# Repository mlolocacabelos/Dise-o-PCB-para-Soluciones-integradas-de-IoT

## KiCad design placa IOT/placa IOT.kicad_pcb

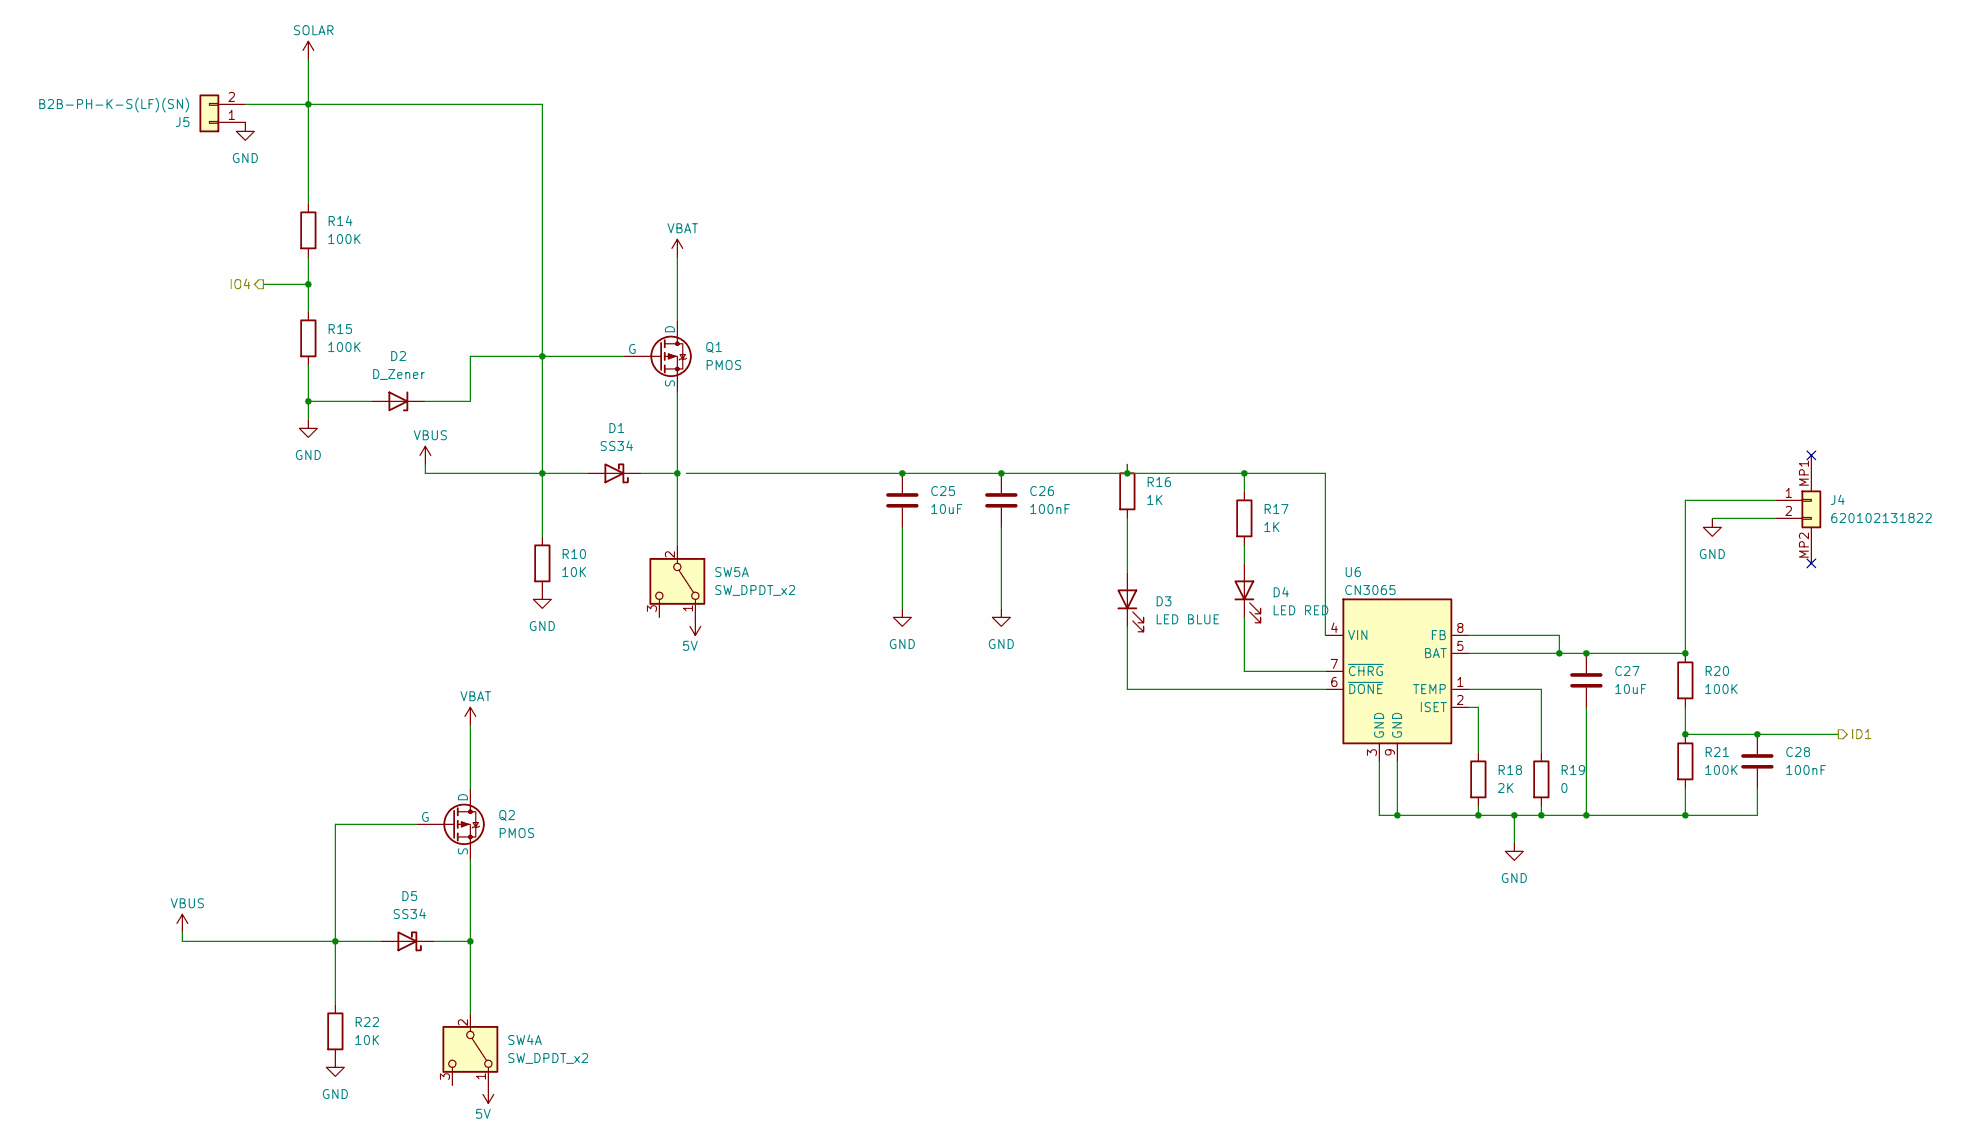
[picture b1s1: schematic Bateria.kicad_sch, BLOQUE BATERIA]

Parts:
C25, C27: 10uF; C_0402_1005Metric
C26, C28: 100nF; C_0402_1005Metric
D1, D5: SS34; D_SMA
D2: D_Zener; D_SOD-123
D3: LED BLUE; LED_0402_1005Metric
D4: LED RED; LED_0402_1005Metric
J4: 620102131822; CONN_SMT_MH_SH_P2.00MM_P2
J5: B2B-PH-K-S(LF)(SN); CONN_THT_MV_JST_P2.00MM_P2
Q1, Q2: PMOS; SOT-23-3
R10, R22: 10K; R_0402_1005Metric
R14, R15, R20, R21: 100K; R_0402_1005Metric
R16, R17: 1K; R_0402_1005Metric
R18: 2K; R_0402_1005Metric
R19: 0; R_0402_1005Metric
SW4, SW5: SW_DPDT_x2; SW_Slide_SPDT_Angled_CK_OS102011MA1Q
U6: CN3065; DFN-8-1EP_3x3mm_P0.5mm_EP1.66x2.38mm

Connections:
5V: SW4.1 (A), SW5.1 (A)
/MCU_WIFIBLU/IO1: C28.1, R20.2, R21.1; also elsewhere on the board
/MCU_WIFIBLU/IO4: R14.2, R15.1; also elsewhere on the board
GND: C25.2, C26.2, C27.2, C28.2, D2.2 (A), J4.2, J5.1, R10.2, R15.2, R18.2, R19.2, R21.2, R22.2, U6.3 (GND), U6.9 (GND); also elsewhere on the board
unnamed: D1.1 (K), Q1.3 (S), SW5.2 (B)
unnamed: D3.2 (A), R16.2
unnamed: D3.1 (K), U6.6 (~DONE)
unnamed: D4.2 (A), R17.2
unnamed: D4.1 (K), U6.7 (~CHRG)
unnamed: D5.1 (K), Q2.3 (S), SW4.2 (B)
unnamed: C27.1, J4.1, R20.1, U6.5 (BAT), U6.8 (FB)
unnamed: R18.1, U6.2 (ISET)
unnamed: R19.1, U6.1 (TEMP)
unnamed: C25.1, C26.1, R16.1, R17.1, U6.4 (VIN)
SOLAR: D1.2 (A), D2.1 (K), D5.2 (A), J5.2, Q1.2 (G), Q2.2 (G), R10.1, R14.1, R22.1; also elsewhere on the board
VBAT: Q1.1 (D), Q2.1 (D); also elsewhere on the board

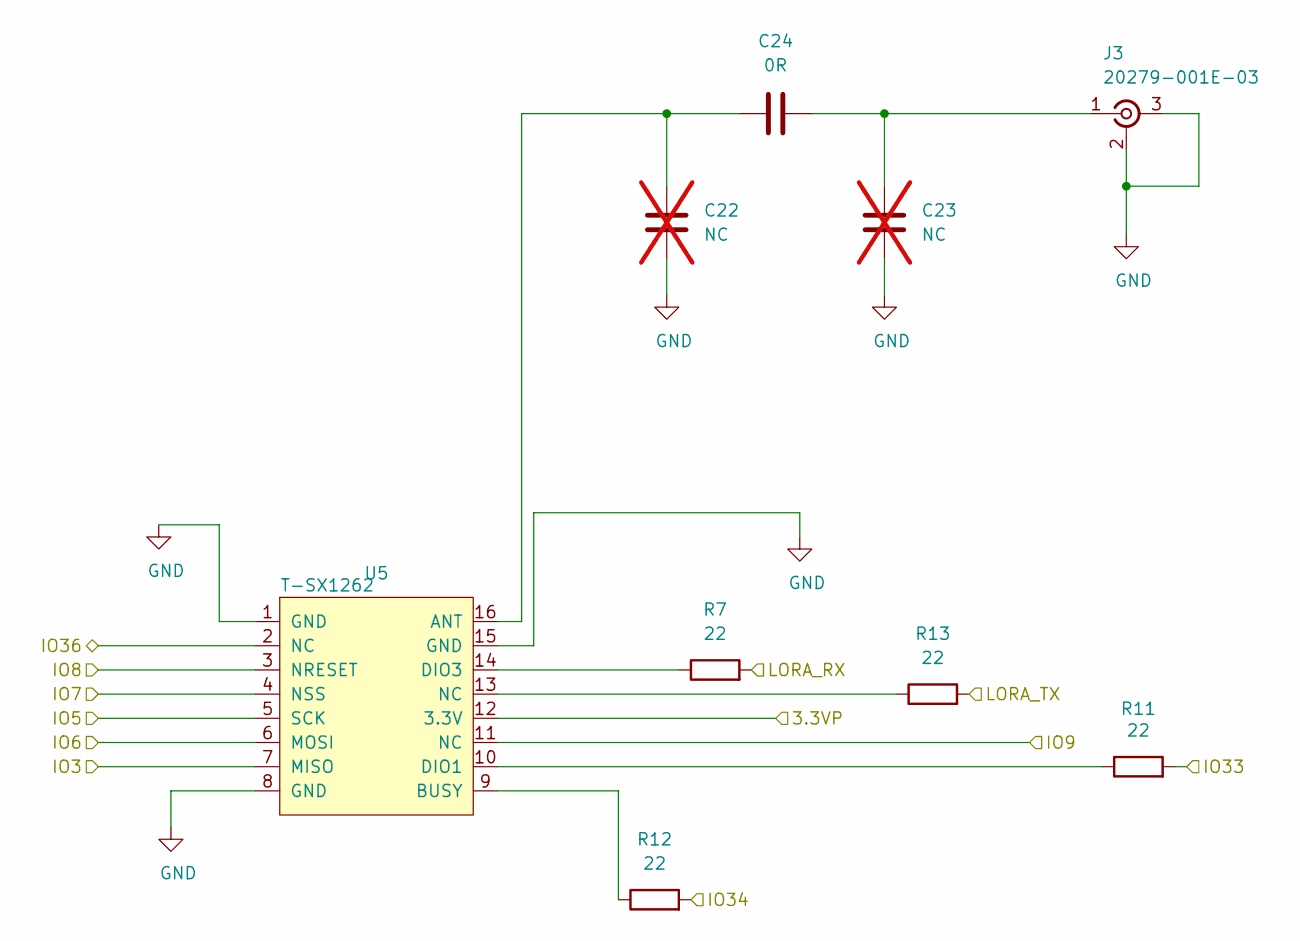
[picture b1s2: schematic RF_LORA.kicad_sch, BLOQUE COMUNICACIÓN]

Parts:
C22, C23: NC; C_0402_1005Metric; not fitted
C24: 0R; C_0402_1005Metric
J3: 20279-001E-03; IPEX_MHF_I
R7, R11, R12, R13: 22; R_0402_1005Metric
U5: T-SX1262; MODULE_T_SX1262

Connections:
/MCU_WIFIBLU/IO3: U5.7 (MISO); also elsewhere on the board
/MCU_WIFIBLU/IO5: U5.5 (SCK); also elsewhere on the board
/MCU_WIFIBLU/IO6: U5.6 (MOSI); also elsewhere on the board
/MCU_WIFIBLU/IO7: U5.4 (NSS); also elsewhere on the board
/MCU_WIFIBLU/IO8: U5.3 (NRESET); also elsewhere on the board
/MCU_WIFIBLU/IO9: U5.11 (NC); also elsewhere on the board
/MCU_WIFIBLU/IO33: R11.2; also elsewhere on the board
/MCU_WIFIBLU/IO34: R12.2; also elsewhere on the board
/MCU_WIFIBLU/IO36: U5.2 (NC); also elsewhere on the board
/MCU_WIFIBLU/LORA_RX: R7.2; also elsewhere on the board
/MCU_WIFIBLU/LORA_TX: R13.2; also elsewhere on the board
/RF_LORA/3.3VP: U5.12 (3.3V)
GND: C22.2, C23.2, J3.2 (Ext), J3.3 (Ext), U5.1 (GND), U5.8 (GND), U5.15 (GND); also elsewhere on the board
unnamed: C23.1, C24.2, J3.1 (In)
unnamed: R13.1, U5.13 (NC)
unnamed: C22.1, C24.1, U5.16 (ANT)
unnamed: R12.1, U5.9 (BUSY)
unnamed: R11.1, U5.10 (DIO1)
unnamed: R7.1, U5.14 (DIO3)

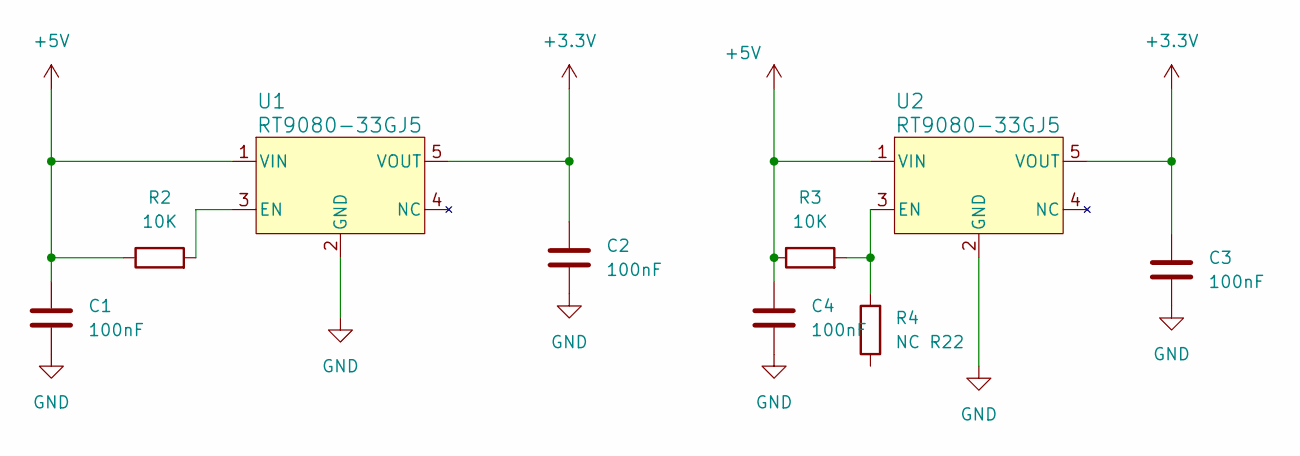
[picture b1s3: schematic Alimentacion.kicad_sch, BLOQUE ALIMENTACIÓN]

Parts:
C1, C2, C3, C4: 100nF; C_0402_1005Metric
R2, R3: 10K; R_0402_1005Metric
R4: NC R22; R_0402_1005Metric
U1, U2: RT9080-33GJ5; TSOT-23-5_RIT

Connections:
+3.3V: C2.1, C3.1, U1.5 (VOUT), U2.5 (VOUT); also elsewhere on the board
+5V: C1.1, C4.1, R2.1, R3.1, U1.1 (VIN), U2.1 (VIN)
GND: C1.2, C2.2, C3.2, C4.2, U1.2 (GND), U2.2 (GND); also elsewhere on the board
unnamed: R2.2, U1.3 (EN)
unnamed: R3.2, R4.2, U2.3 (EN)

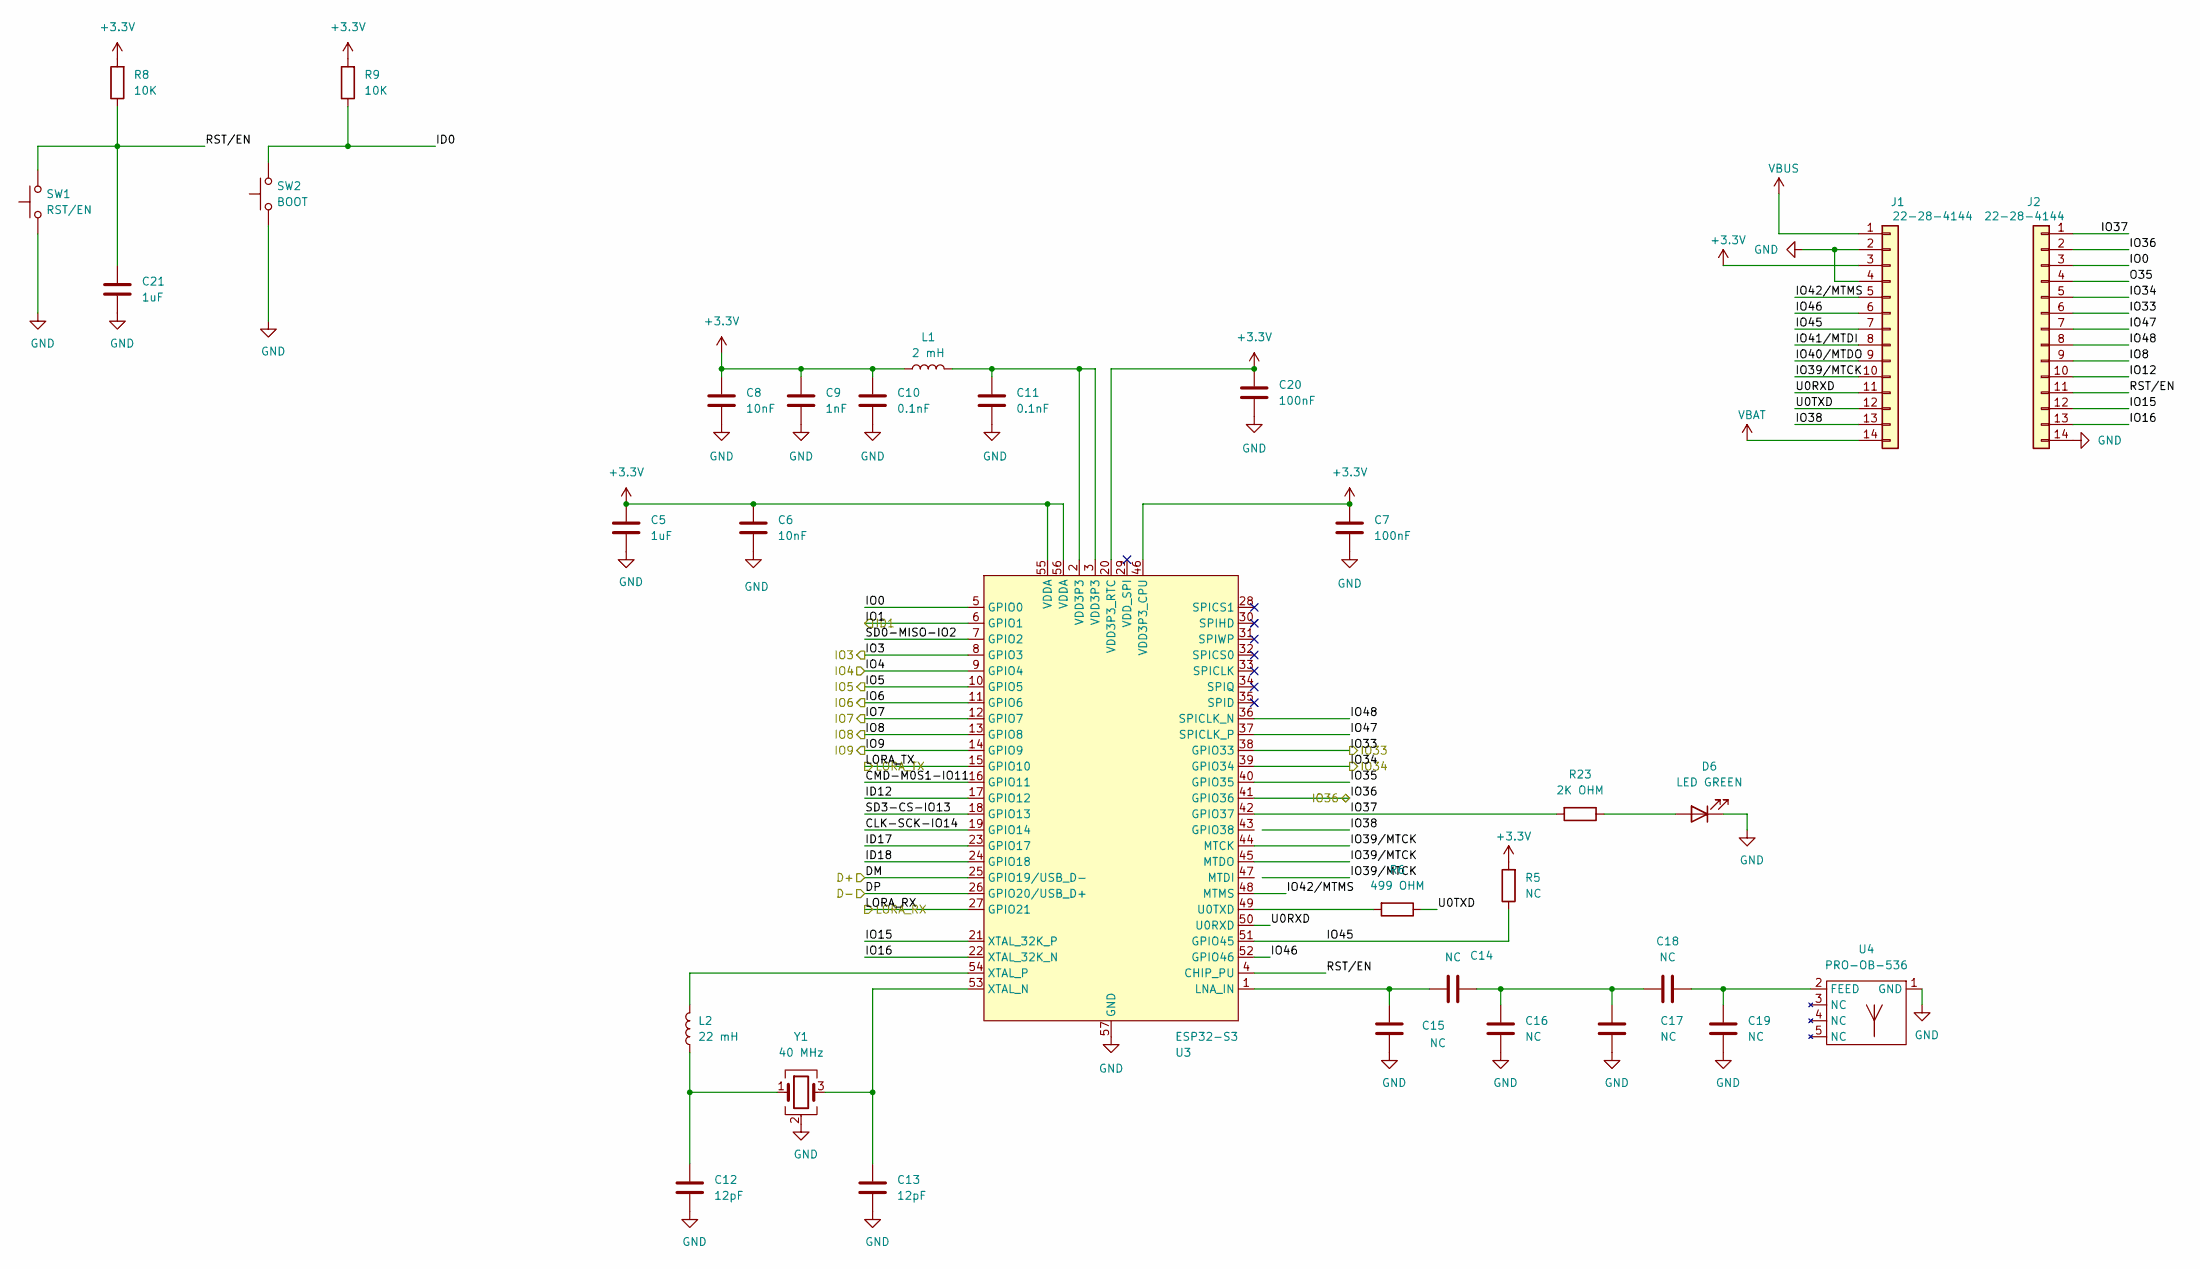
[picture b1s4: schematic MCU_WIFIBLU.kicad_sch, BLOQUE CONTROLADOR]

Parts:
C5, C21: 1uF; C_0402_1005Metric
C6, C8: 10nF; C_0402_1005Metric
C7, C20: 100nF; C_0402_1005Metric
C9: 1nF; C_0402_1005Metric
C10, C11: 0.1nF; C_0402_1005Metric
C12, C13: 12pF; C_0402_1005Metric
C14, C15, C16, C17, C18, C19: NC; C_0402_1005Metric
D6: LED GREEN; LED_0402_1005Metric
J1, J2: 22-28-4144; CONN_THT_MV_PH_P2.54MM_P14
L1: 2 mH; L_0402_1005Metric
L2: 22 mH; L_0402_1005Metric
R5: NC; R_0402_1005Metric
R6: 499 OHM; R_0402_1005Metric
R8, R9: 10K; R_0402_1005Metric
R23: 2K OHM; R_0402_1005Metric
SW1: RST/EN; SW_Push_SPST_NO_Alps_SKRK
SW2: BOOT; SW_Push_SPST_NO_Alps_SKRK
U3: ESP32-S3; QFN-56-1EP_7x7mm_P0.4mm_EP4x4mm
U4: PRO-OB-536; ANTENNA_PIFA_3D_2.4GHZ
Y1: 40 MHz; Crystal_SMD_3225-4Pin_3.2x2.5mm

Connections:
+3.3V: C5.1, C6.1, C7.1, C8.1, C9.1, C10.1, C20.1, J1.3, L1.1, R5.2, R8.2, R9.2, U3.20 (VDD3P3_RTC), U3.46 (VDD3P3_CPU), U3.55 (VDDA), U3.56 (VDDA); also elsewhere on the board
/MCU_WIFIBLU/CLK-SCK-IO14: U3.19 (GPIO14)
/MCU_WIFIBLU/CMD-M0S1-IO11: U3.16 (GPIO11)
/MCU_WIFIBLU/DM: U3.25 (GPIO19/USB_D-); also elsewhere on the board
/MCU_WIFIBLU/DP: U3.26 (GPIO20/USB_D+); also elsewhere on the board
/MCU_WIFIBLU/ID0: R9.1, SW2.2
/MCU_WIFIBLU/ID12: U3.17 (GPIO12)
/MCU_WIFIBLU/ID17: U3.23 (GPIO17)
/MCU_WIFIBLU/ID18: U3.24 (GPIO18)
/MCU_WIFIBLU/IO0: J2.3, U3.5 (GPIO0)
/MCU_WIFIBLU/IO1: U3.6 (GPIO1); also elsewhere on the board
/MCU_WIFIBLU/IO3: U3.8 (GPIO3); also elsewhere on the board
/MCU_WIFIBLU/IO4: U3.9 (GPIO4); also elsewhere on the board
/MCU_WIFIBLU/IO5: U3.10 (GPIO5); also elsewhere on the board
/MCU_WIFIBLU/IO6: U3.11 (GPIO6); also elsewhere on the board
/MCU_WIFIBLU/IO7: U3.12 (GPIO7); also elsewhere on the board
/MCU_WIFIBLU/IO8: J2.9, U3.13 (GPIO8); also elsewhere on the board
/MCU_WIFIBLU/IO9: U3.14 (GPIO9); also elsewhere on the board
/MCU_WIFIBLU/IO12: J2.10
/MCU_WIFIBLU/IO15: J2.12, U3.21 (XTAL_32K_P)
/MCU_WIFIBLU/IO16: J2.13, U3.22 (XTAL_32K_N)
/MCU_WIFIBLU/IO33: J2.6, U3.38 (GPIO33); also elsewhere on the board
/MCU_WIFIBLU/IO34: J2.5, U3.39 (GPIO34); also elsewhere on the board
/MCU_WIFIBLU/IO35: U3.40 (GPIO35)
/MCU_WIFIBLU/IO36: J2.2, U3.41 (GPIO36); also elsewhere on the board
/MCU_WIFIBLU/IO37: J2.1, R23.2, U3.42 (GPIO37)
/MCU_WIFIBLU/IO38: J1.13
/MCU_WIFIBLU/IO39/MTCK: J1.10, U3.44 (MTCK), U3.45 (MTDO)
/MCU_WIFIBLU/IO40/MTDO: J1.9
/MCU_WIFIBLU/IO41/MTDI: J1.8
/MCU_WIFIBLU/IO42/MTMS: J1.5, U3.48 (MTMS)
/MCU_WIFIBLU/IO45: J1.7, R5.1, U3.51 (GPIO45)
/MCU_WIFIBLU/IO46: J1.6, U3.52 (GPIO46)
/MCU_WIFIBLU/IO47: J2.7, U3.37 (SPICLK_P)
/MCU_WIFIBLU/IO48: J2.8, U3.36 (SPICLK_N)
/MCU_WIFIBLU/LORA_RX: U3.27 (GPIO21); also elsewhere on the board
/MCU_WIFIBLU/LORA_TX: U3.15 (GPIO10); also elsewhere on the board
/MCU_WIFIBLU/O35: J2.4
/MCU_WIFIBLU/RST/EN: C21.1, J2.11, R8.1, SW1.2, U3.4 (CHIP_PU)
/MCU_WIFIBLU/SD0-MISO-IO2: U3.7 (GPIO2)
/MCU_WIFIBLU/SD3-CS-IO13: U3.18 (GPIO13)
/MCU_WIFIBLU/U0RXD: J1.11, U3.50 (U0RXD)
/MCU_WIFIBLU/U0TXD: J1.12, R6.1
GND: C5.2, C6.2, C7.2, C8.2, C9.2, C10.2, C11.2, C12.2, C13.2, C15.2, C16.2, C17.2, C19.2, C20.2, C21.2, D6.1 (K), J1.2, J1.4, J2.14, SW1.1, SW2.1, U3.57 (GND), U4.1 (GND), Y1.2 (G), Y1.4 (G); also elsewhere on the board
unnamed: C11.1, L1.2, U3.2 (VDD3P3), U3.3 (VDD3P3)
unnamed: C12.1, L2.1, Y1.1
unnamed: C14.2, C16.1, C17.1, C18.1
unnamed: D6.2 (A), R23.1
unnamed: C14.1, C15.1, U3.1 (LNA_IN)
unnamed: R6.2, U3.49 (U0TXD)
unnamed: C13.1, U3.53 (XTAL_N), Y1.3
unnamed: L2.2, U3.54 (XTAL_P)
unnamed: C18.2, C19.1, U4.2 (FEED)
SOLAR: J1.1; also elsewhere on the board
VBAT: J1.14; also elsewhere on the board

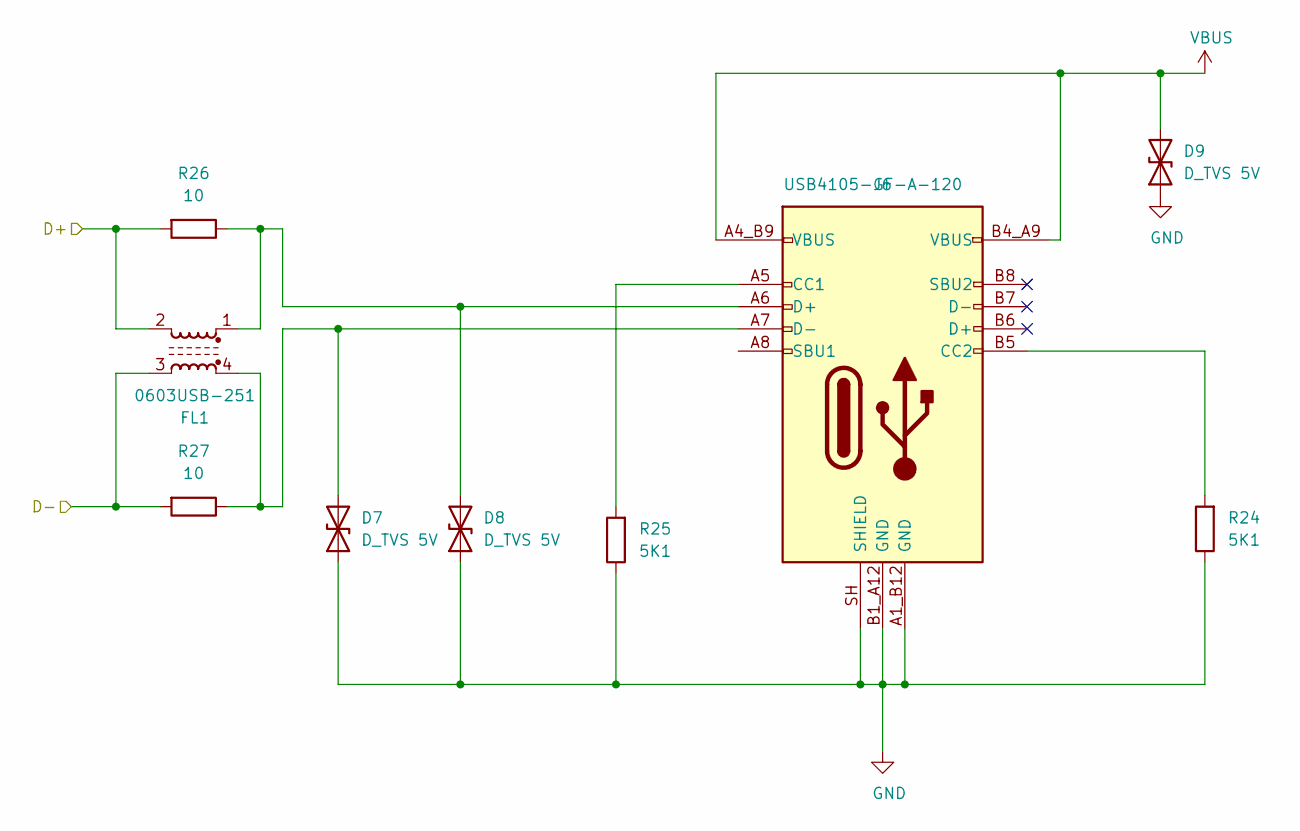
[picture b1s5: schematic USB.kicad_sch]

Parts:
D7, D8, D9: D_TVS 5V; D_SOD-882
FL1: 0603USB-251; L_CommonModeChoke_Coilcraft_0603USB
J6: USB4105-GF-A-120; CONN_SMT_RH_USBC_P0.50MM_P16
R24, R25: 5K1; R_0402_1005Metric
R26, R27: 10; R_0402_1005Metric

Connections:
/MCU_WIFIBLU/DM: FL1.2, R26.2; also elsewhere on the board
/MCU_WIFIBLU/DP: FL1.3, R27.2; also elsewhere on the board
GND: D7.1 (A1), D8.1 (A1), D9.1 (A1), J6.A1_B12 (GND), J6.B1_A12 (GND), J6.SH (SHIELD), R24.1, R25.1; also elsewhere on the board
unnamed: D7.2 (A2), FL1.4, J6.A7 (D-), R27.1
unnamed: D8.2 (A2), FL1.1, J6.A6 (D+), R26.1
unnamed: J6.A5 (CC1), R25.2
unnamed: J6.B5 (CC2), R24.2
SOLAR: D9.2 (A2), J6.A4_B9 (VBUS), J6.B4_A9 (VBUS); also elsewhere on the board

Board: 4 copper layers, 89 parts (0 on the bottom side), 66 nets, no tracks yet.

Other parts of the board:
M1, M2, M3, M4: MountingHole_2.5mm_Pad_TopBottom

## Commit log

2026-05-18 library add
2026-05-18 Project created v1
2026-05-19 resistencia añadida
2026-05-19 ESQUEMATICO AÑADIDO
2026-05-19 ESQUEMATICO IOT
2026-05-19 ALIMENTACION
2026-05-19 MICROCONTROLADOR EN PROCESO
2026-05-20 MICROCONTROLADOR TERMINADO
2026-05-20 RF TERMINADO
2026-05-20 MICROCONTROLADOR TERMINADOCON CAMBIO
2026-05-20 USB TERMINADO
2026-05-20 BATERIA TERMINADA
2026-05-20 ACABADO
2026-05-20 ULTIMA PRUEBA
2026-05-21 ULTIMA PRUEBA2
